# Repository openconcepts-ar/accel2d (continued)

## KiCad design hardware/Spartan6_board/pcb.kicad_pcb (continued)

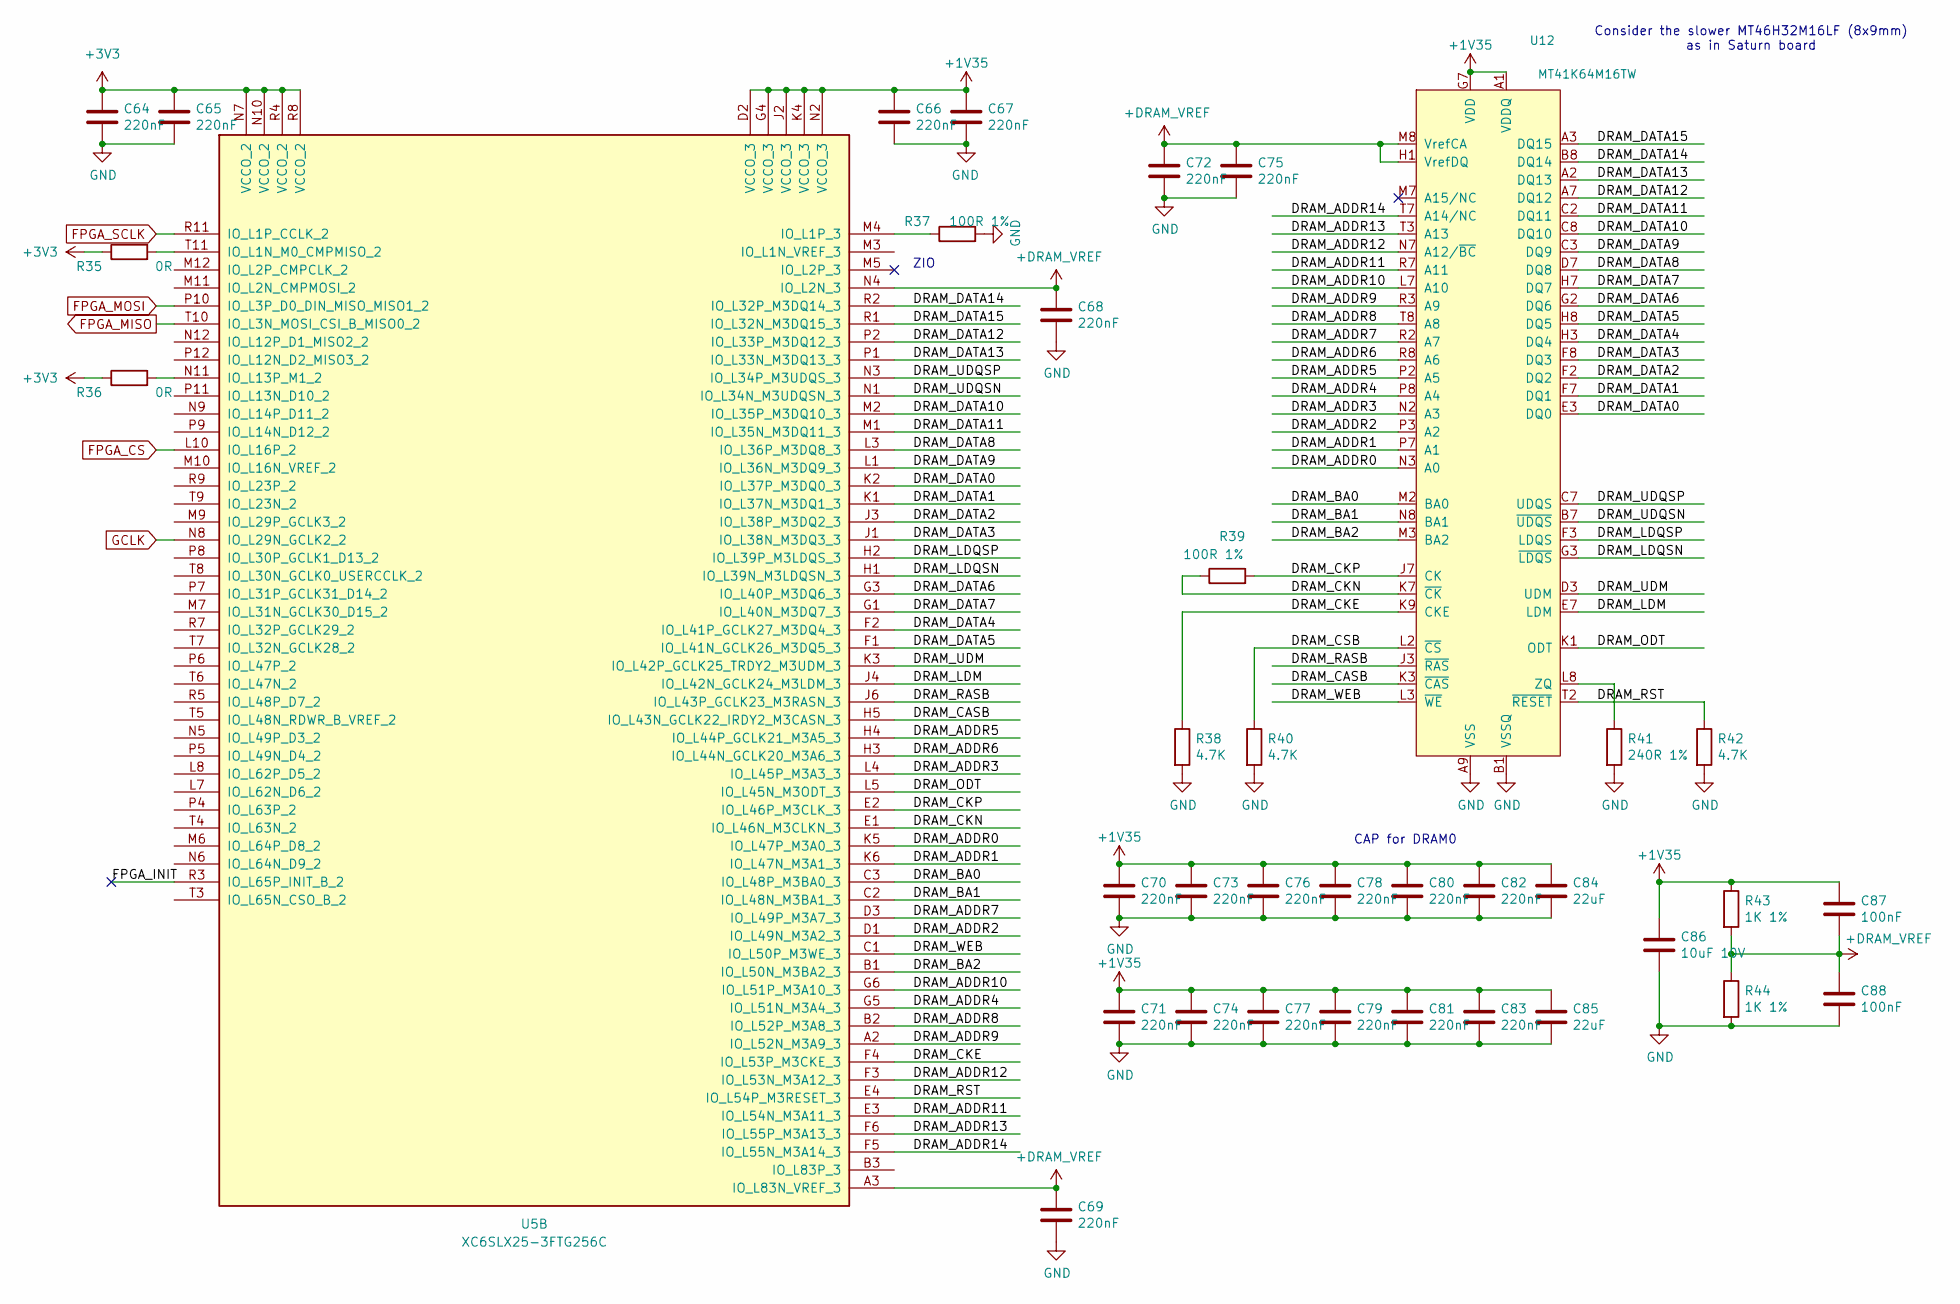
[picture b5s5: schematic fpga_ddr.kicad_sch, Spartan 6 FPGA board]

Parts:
C64, C65, C66, C67, C68, C69, C70, C71, C72, C73, C74, C75, C76, C77, C78, C79, C80, C81, C82, C83: 220nF; C_0402_1005Metric; LCSC C880414
C84, C85: 22uF; C_0603_1608Metric; LCSC Part Number C86295
C86: 10uF 10V; C_0805_2012Metric; LCSC Part Number C15850
C87, C88: 100nF; C_0402_1005Metric; LCSC C56392
R35, R36: 0R; R_0402_1005Metric; LCSC C105870
R37, R39: 100R 1%; R_0402_1005Metric
R38, R40, R42: 4.7K; R_0402_1005Metric; LCSC C105870
R41: 240R 1%; R_0402_1005Metric
R43, R44: 1K 1%; R_0402_1005Metric
U5: XC6SLX25-3FTG256C; Xilinx_FTG256; LCSC Part Number C1521716
U12: MT41K64M16TW; BGA-96_9.0x14.0mm_P0.8mm; LCSC Part Number C524855

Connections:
+1V35: C66.1, C67.1, C70.1, C71.1, C73.1, C74.1, C76.1, C77.1, C78.1, C79.1, C80.1, C81.1, C82.1, C83.1, C84.1, C85.1, C86.1, C87.1, R43.1, U5.D2 (VCCO_3), U5.G4 (VCCO_3), U5.J2 (VCCO_3), U5.K4 (VCCO_3), U5.N2 (VCCO_3), U12.A1 (VDDQ), U12.A8 (VDDQ), U12.B2 (VDD), U12.C1 (VDDQ), U12.C9 (VDDQ), U12.D2 (VDDQ), U12.D9 (VDD), U12.E9 (VDDQ), U12.F1 (VDDQ), U12.G7 (VDD), U12.H2 (VDDQ), U12.H9 (VDDQ), U12.K2 (VDD), U12.K8 (VDD), U12.N1 (VDD), U12.N9 (VDD), U12.R1 (VDD), U12.R9 (VDD); also elsewhere on the board
+3V3: C64.1, C65.1, R35.1, R36.1, U5.N7 (VCCO_2), U5.N10 (VCCO_2), U5.R4 (VCCO_2), U5.R8 (VCCO_2); also elsewhere on the board
+DRAM_VREF: C68.1, C69.1, C72.1, C75.1, C87.2, C88.1, R43.2, R44.1, U5.A3 (IO_L83N_VREF_3), U5.N4 (IO_L2N_3), U12.H1 (VrefDQ), U12.M8 (VrefCA)
/fpga_ddr/DRAM_ADDR0: U5.K5 (IO_L47P_M3A0_3), U12.N3 (A0)
/fpga_ddr/DRAM_ADDR1: U5.K6 (IO_L47N_M3A1_3), U12.P7 (A1)
/fpga_ddr/DRAM_ADDR2: U5.D1 (IO_L49N_M3A2_3), U12.P3 (A2)
/fpga_ddr/DRAM_ADDR3: U5.L4 (IO_L45P_M3A3_3), U12.N2 (A3)
/fpga_ddr/DRAM_ADDR4: U5.G5 (IO_L51N_M3A4_3), U12.P8 (A4)
/fpga_ddr/DRAM_ADDR5: U5.H4 (IO_L44P_GCLK21_M3A5_3), U12.P2 (A5)
/fpga_ddr/DRAM_ADDR6: U5.H3 (IO_L44N_GCLK20_M3A6_3), U12.R8 (A6)
/fpga_ddr/DRAM_ADDR7: U5.D3 (IO_L49P_M3A7_3), U12.R2 (A7)
/fpga_ddr/DRAM_ADDR8: U5.B2 (IO_L52P_M3A8_3), U12.T8 (A8)
/fpga_ddr/DRAM_ADDR9: U5.A2 (IO_L52N_M3A9_3), U12.R3 (A9)
/fpga_ddr/DRAM_ADDR10: U5.G6 (IO_L51P_M3A10_3), U12.L7 (A10)
/fpga_ddr/DRAM_ADDR11: U5.E3 (IO_L54N_M3A11_3), U12.R7 (A11)
/fpga_ddr/DRAM_ADDR12: U5.F3 (IO_L53N_M3A12_3), U12.N7 (A12/~BC)
/fpga_ddr/DRAM_ADDR13: U5.F6 (IO_L55P_M3A13_3), U12.T3 (A13)
/fpga_ddr/DRAM_ADDR14: U5.F5 (IO_L55N_M3A14_3), U12.T7 (A14/NC)
/fpga_ddr/DRAM_BA0: U5.C3 (IO_L48P_M3BA0_3), U12.M2 (BA0)
/fpga_ddr/DRAM_BA1: U5.C2 (IO_L48N_M3BA1_3), U12.N8 (BA1)
/fpga_ddr/DRAM_BA2: U5.B1 (IO_L50N_M3BA2_3), U12.M3 (BA2)
/fpga_ddr/DRAM_CASB: U5.H5 (IO_L43N_GCLK22_IRDY2_M3CASN_3), U12.K3 (~CAS)
/fpga_ddr/DRAM_CKE: R38.1, U5.F4 (IO_L53P_M3CKE_3), U12.K9 (CKE)
/fpga_ddr/DRAM_CKN: R39.1, U5.E1 (IO_L46N_M3CLKN_3), U12.K7 (~CK)
/fpga_ddr/DRAM_CKP: R39.2, U5.E2 (IO_L46P_M3CLK_3), U12.J7 (CK)
/fpga_ddr/DRAM_CSB: R40.1, U12.L2 (~CS)
/fpga_ddr/DRAM_DATA0: U5.K2 (IO_L37P_M3DQ0_3), U12.E3 (DQ0)
/fpga_ddr/DRAM_DATA1: U5.K1 (IO_L37N_M3DQ1_3), U12.F7 (DQ1)
/fpga_ddr/DRAM_DATA2: U5.J3 (IO_L38P_M3DQ2_3), U12.F2 (DQ2)
/fpga_ddr/DRAM_DATA3: U5.J1 (IO_L38N_M3DQ3_3), U12.F8 (DQ3)
/fpga_ddr/DRAM_DATA4: U5.F2 (IO_L41P_GCLK27_M3DQ4_3), U12.H3 (DQ4)
/fpga_ddr/DRAM_DATA5: U5.F1 (IO_L41N_GCLK26_M3DQ5_3), U12.H8 (DQ5)
/fpga_ddr/DRAM_DATA6: U5.G3 (IO_L40P_M3DQ6_3), U12.G2 (DQ6)
/fpga_ddr/DRAM_DATA7: U5.G1 (IO_L40N_M3DQ7_3), U12.H7 (DQ7)
/fpga_ddr/DRAM_DATA8: U5.L3 (IO_L36P_M3DQ8_3), U12.D7 (DQ8)
/fpga_ddr/DRAM_DATA9: U5.L1 (IO_L36N_M3DQ9_3), U12.C3 (DQ9)
/fpga_ddr/DRAM_DATA10: U5.M2 (IO_L35P_M3DQ10_3), U12.C8 (DQ10)
/fpga_ddr/DRAM_DATA11: U5.M1 (IO_L35N_M3DQ11_3), U12.C2 (DQ11)
/fpga_ddr/DRAM_DATA12: U5.P2 (IO_L33P_M3DQ12_3), U12.A7 (DQ12)
/fpga_ddr/DRAM_DATA13: U5.P1 (IO_L33N_M3DQ13_3), U12.A2 (DQ13)
/fpga_ddr/DRAM_DATA14: U5.R2 (IO_L32P_M3DQ14_3), U12.B8 (DQ14)
/fpga_ddr/DRAM_DATA15: U5.R1 (IO_L32N_M3DQ15_3), U12.A3 (DQ15)
/fpga_ddr/DRAM_LDM: U5.J4 (IO_L42N_GCLK24_M3LDM_3), U12.E7 (LDM)
/fpga_ddr/DRAM_LDQSN: U5.H1 (IO_L39N_M3LDQSN_3), U12.G3 (~LDQS)
/fpga_ddr/DRAM_LDQSP: U5.H2 (IO_L39P_M3LDQS_3), U12.F3 (LDQS)
/fpga_ddr/DRAM_ODT: U5.L5 (IO_L45N_M3ODT_3), U12.K1 (ODT)
/fpga_ddr/DRAM_RASB: U5.J6 (IO_L43P_GCLK23_M3RASN_3), U12.J3 (~RAS)
/fpga_ddr/DRAM_RST: R42.1, U5.E4 (IO_L54P_M3RESET_3), U12.T2 (~RESET)
/fpga_ddr/DRAM_UDM: U5.K3 (IO_L42P_GCLK25_TRDY2_M3UDM_3), U12.D3 (UDM)
/fpga_ddr/DRAM_UDQSN: U5.N1 (IO_L34N_M3UDQSN_3), U12.B7 (~UDQS)
/fpga_ddr/DRAM_UDQSP: U5.N3 (IO_L34P_M3UDQS_3), U12.C7 (UDQS)
/fpga_ddr/DRAM_WEB: U5.C1 (IO_L50P_M3WE_3), U12.L3 (~WE)
/fpga_ddr/FPGA_INIT: U5.R3 (IO_L65P_INIT_B_2)
FPGA_CS: U5.L10 (IO_L16P_2); also elsewhere on the board
FPGA_MISO: U5.T10 (IO_L3N_MOSI_CSI_B_MISO0_2); also elsewhere on the board
FPGA_MOSI: U5.P10 (IO_L3P_D0_DIN_MISO_MISO1_2); also elsewhere on the board
FPGA_SCLK: U5.R11 (IO_L1P_CCLK_2); also elsewhere on the board
GCLK: U5.N8 (IO_L29N_GCLK2_2); also elsewhere on the board
GND: C64.2, C65.2, C66.2, C67.2, C68.2, C69.2, C70.2, C71.2, C72.2, C73.2, C74.2, C75.2, C76.2, C77.2, C78.2, C79.2, C80.2, C81.2, C82.2, C83.2, C84.2, C85.2, C86.2, C88.2, R37.2, R38.2, R40.2, R41.2, R42.2, R44.2, U12.A9 (VSS), U12.B1 (VSSQ), U12.B3 (VSS), U12.B9 (VSSQ), U12.D1 (VSSQ), U12.D8 (VSSQ), U12.E1 (VSS), U12.E2 (VSSQ), U12.E8 (VSSQ), U12.F9 (VSSQ), U12.G1 (VSSQ), U12.G8 (VSS), U12.G9 (VSSQ), U12.J1 (VSS), U12.J2 (VSS), U12.J8 (VSS), U12.J9 (VSS), U12.L1 (VSS), U12.L9 (VSS), U12.M1 (VSS), U12.M9 (VSS), U12.P1 (VSS), U12.P9 (VSS), U12.T1 (VSS), U12.T9 (VSS); also elsewhere on the board
unnamed: R35.2, U5.T11 (IO_L1N_M0_CMPMISO_2)
unnamed: R37.1, U5.M4 (IO_L1P_3)
unnamed: R36.2, U5.N11 (IO_L13P_M1_2)
unnamed: R41.1, U12.L8 (ZQ)

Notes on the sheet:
Consider the slower MT46H32M16LF (8x9mm) as in Saturn board
ZIO
CAP for DRAM0

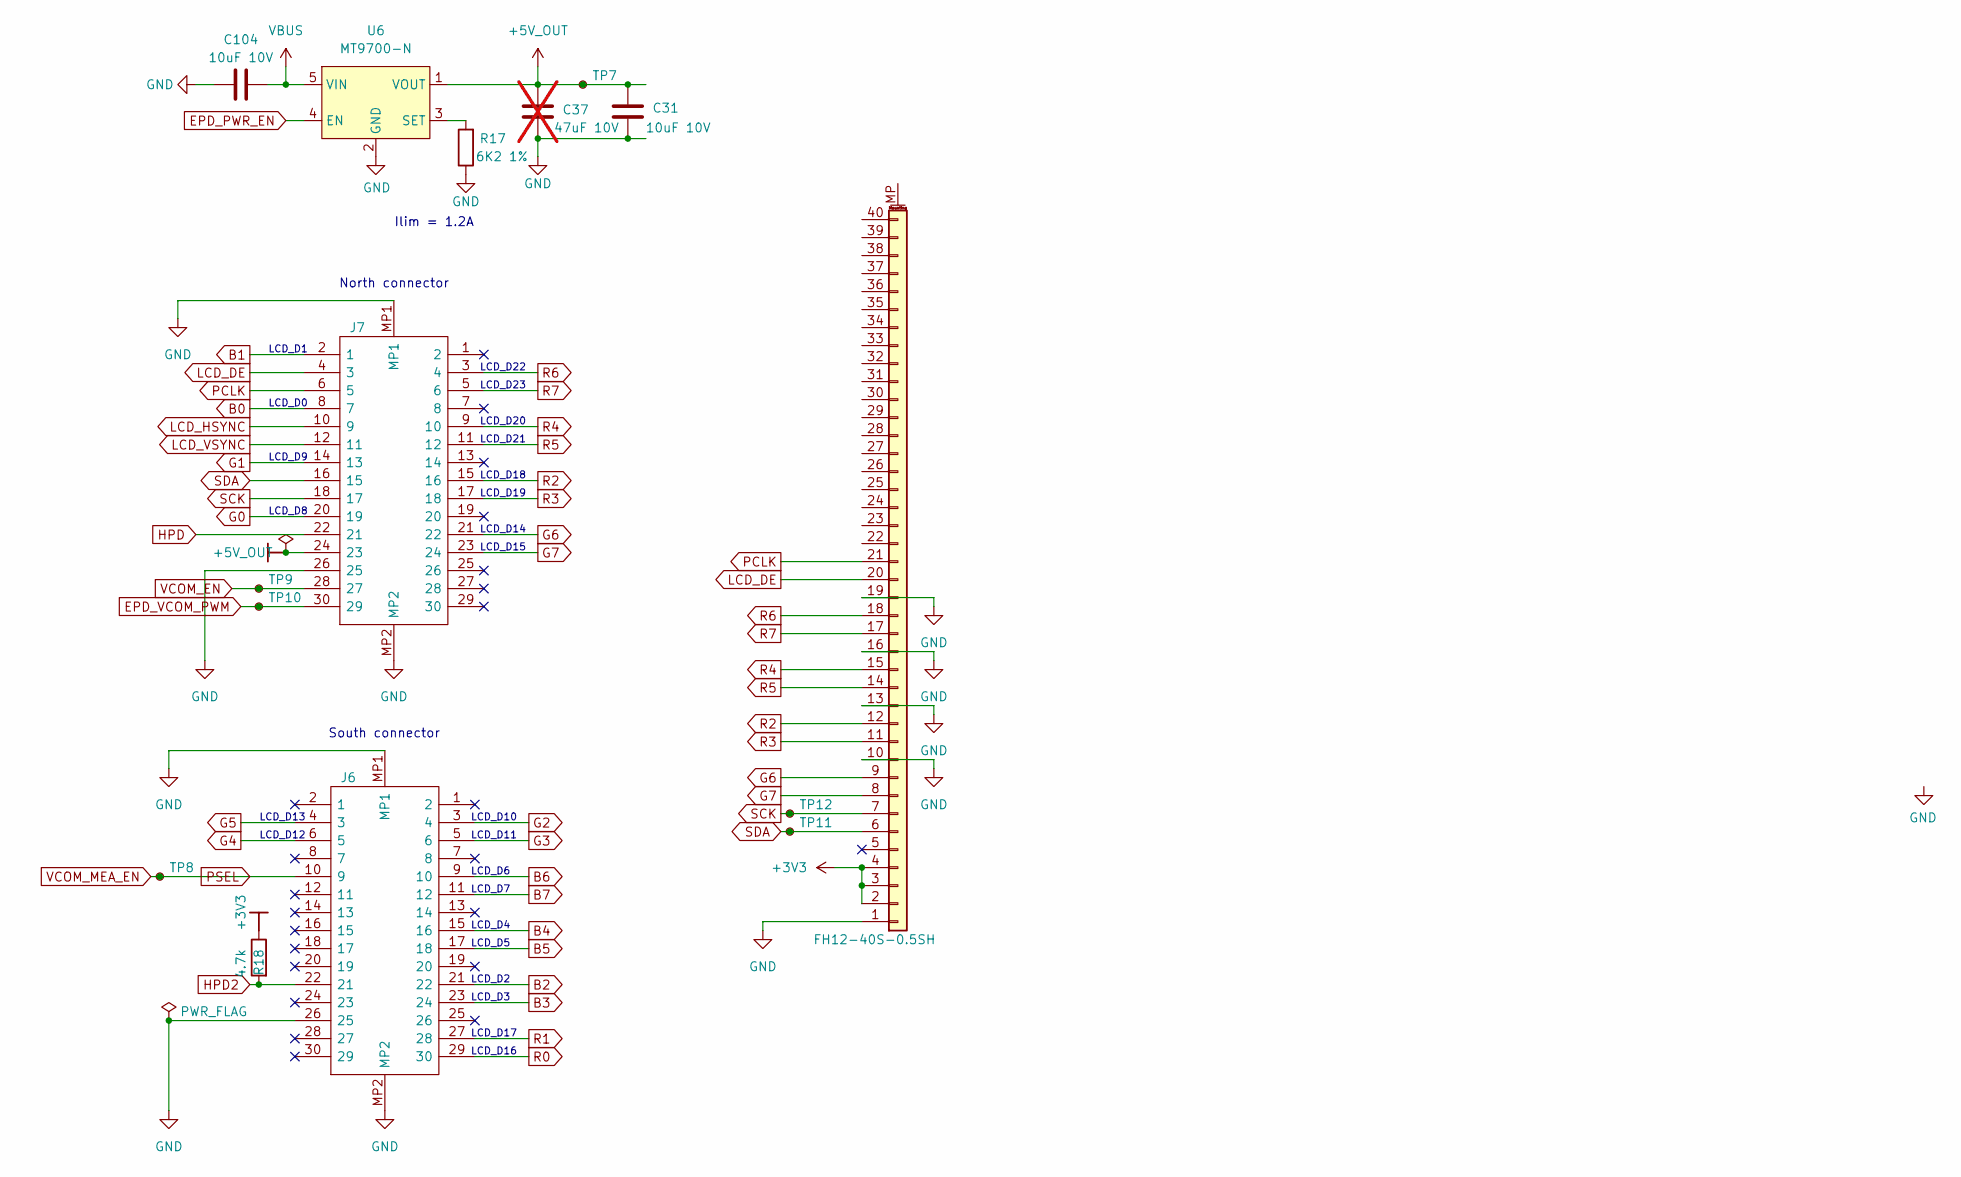
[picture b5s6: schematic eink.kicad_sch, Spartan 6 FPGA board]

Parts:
C31, C104: 10uF 10V; C_0805_2012Metric
C37: 47uF 10V; C_1206_3216Metric; LCSC Part Number C96123; not fitted
J3: FH12-40S-0.5SH; Hirose_FH12-40S-0.5SH_1x40-1MP_P0.50mm_Horizontal_Reversed; MPN FH12-40S-0.5SH
J6, J7: DF12NB(3.0)-30DS-0.5V(51); DF12NB3030DP05V51; MPN DF12NB(3.0)-30DS-0.5V(51)
R17: 6K2 1%; R_0402_1005Metric
R18: 4.7k; R_0402_1005Metric; LCSC Part Number C25940
TP7, TP8, TP9, TP10, TP11, TP12: TestPoint_Small; TestPoint_Pad_D1.5mm
U6: MT9700-N; SOT-23-5; MPN MT9700-N; LCSC Part Number C42441843

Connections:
+3V3: J3.2, J3.3, J3.4, R18.1; also elsewhere on the board
+5V_OUT: C31.1, C37.2, J7.24 (23), TP7.1, U6.1 (VOUT)
B0: J7.8 (7); also elsewhere on the board
B1: J7.2 (1); also elsewhere on the board
B2: J6.21 (22); also elsewhere on the board
B3: J6.23 (24); also elsewhere on the board
B4: J6.15 (16); also elsewhere on the board
B5: J6.17 (18); also elsewhere on the board
B6: J6.9 (10); also elsewhere on the board
B7: J6.11 (12); also elsewhere on the board
EPD_PWR_EN: U6.4 (EN); also elsewhere on the board
EPD_VCOM_PWM: J7.30 (29), TP10.1; also elsewhere on the board
G0: J7.20 (19); also elsewhere on the board
G1: J7.14 (13); also elsewhere on the board
G2: J6.3 (4); also elsewhere on the board
G3: J6.5 (6); also elsewhere on the board
G4: J6.6 (5); also elsewhere on the board
G5: J6.4 (3); also elsewhere on the board
G6: J3.9, J7.21 (22); also elsewhere on the board
G7: J3.8, J7.23 (24); also elsewhere on the board
GND: C31.2, C37.1, C104.1, J3.1, J3.10, J3.13, J3.16, J3.19, J6.26 (25), J6.MP1, J6.MP2, J7.26 (25), J7.MP1, J7.MP2, R17.1, U6.2 (GND); also elsewhere on the board
HPD: J7.22 (21)
HPD2: J6.22 (21), R18.2
LCD_DE: J3.20, J7.4 (3); also elsewhere on the board
LCD_HSYNC: J7.10 (9); also elsewhere on the board
LCD_VSYNC: J7.12 (11); also elsewhere on the board
unnamed: R17.2, U6.3 (SET)
PCLK: J3.21, J7.6 (5); also elsewhere on the board
PSEL: J6.10 (9), TP8.1; also elsewhere on the board
R2: J3.12, J7.15 (16); also elsewhere on the board
R3: J3.11, J7.17 (18); also elsewhere on the board
R4: J3.15, J7.9 (10); also elsewhere on the board
R5: J3.14, J7.11 (12); also elsewhere on the board
R6: J3.18, J7.3 (4); also elsewhere on the board
R7: J3.17, J7.5 (6); also elsewhere on the board
SCK: J3.7, J7.18 (17), TP12.1
SDA: J3.6, J7.16 (15), TP11.1
VBUS: C104.2, U6.5 (VIN); also elsewhere on the board
VCOM_EN: J7.28 (27), TP9.1; also elsewhere on the board

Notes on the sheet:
LCD_D0
Ilim = 1.2A
LCD_D17
South connector
LCD_D11
LCD_D4
LCD_D3
LCD_D8
LCD_D10
LCD_D19
LCD_D23
LCD_D20
North connector
LCD_D5
LCD_D13
LCD_D18
LCD_D21
LCD_D22
LCD_D7
LCD_D6
LCD_D15
LCD_D1
LCD_D12
LCD_D9
LCD_D16
LCD_D2
LCD_D14

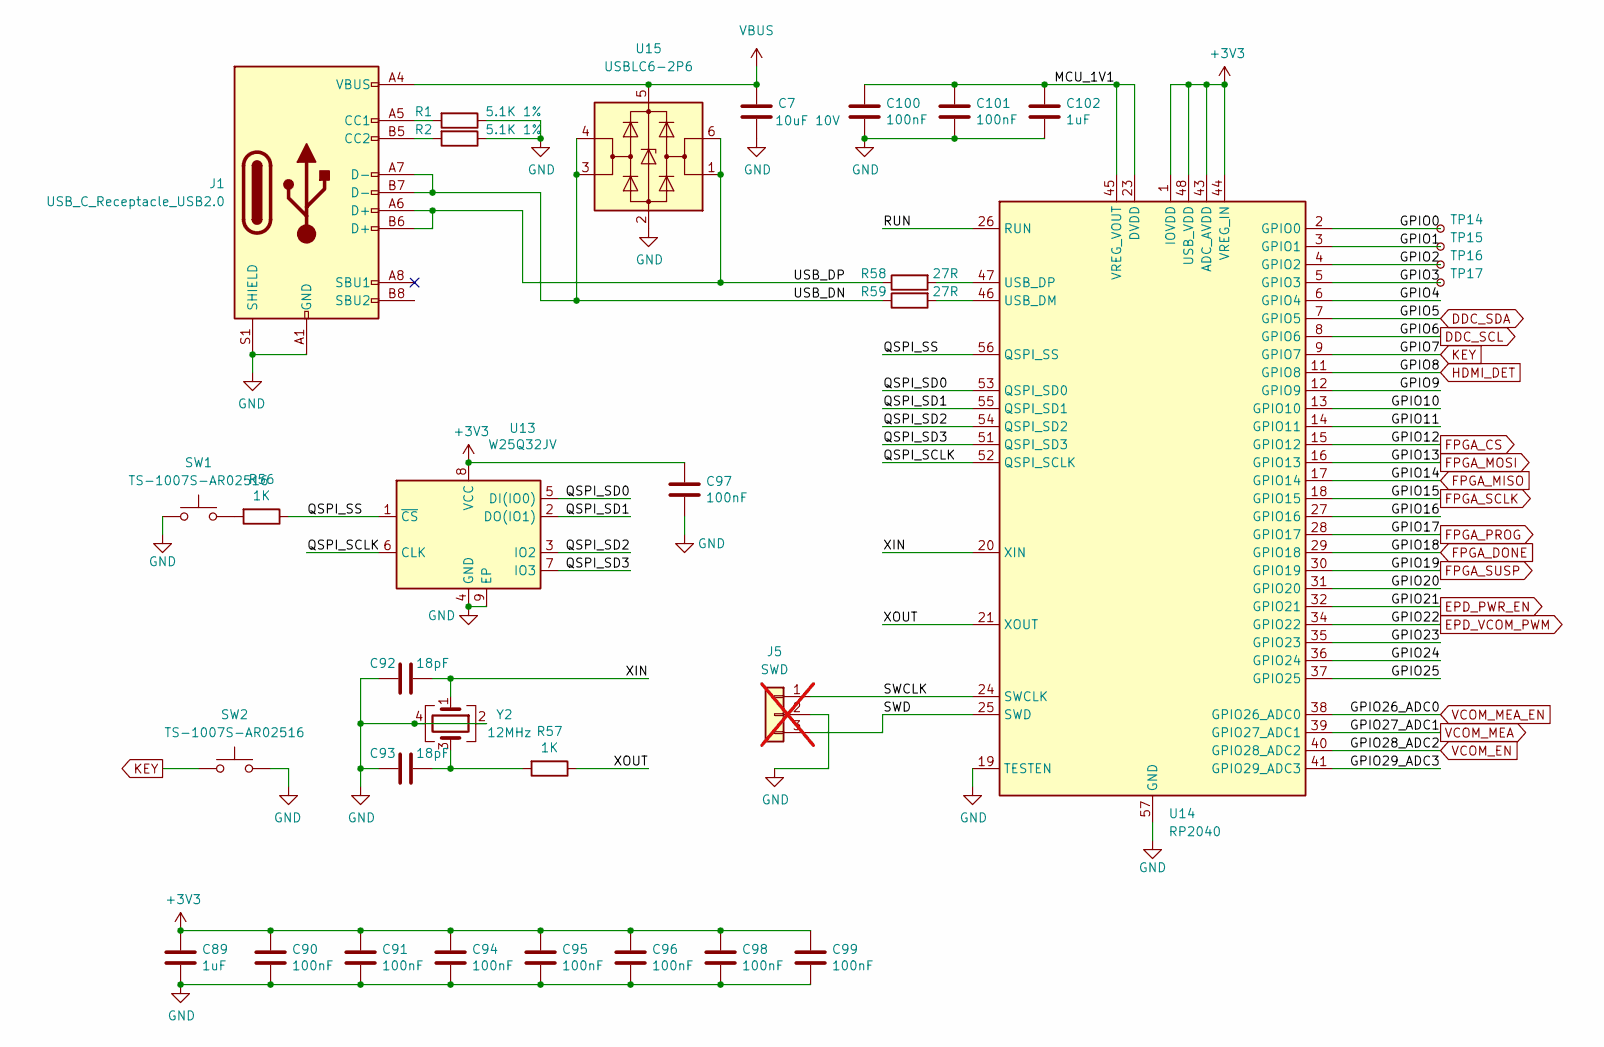
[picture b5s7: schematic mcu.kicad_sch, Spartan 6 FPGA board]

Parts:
C7: 10uF 10V; C_0805_2012Metric; LCSC Part Number C32635
C89, C102: 1uF; C_0402_1005Metric
C90, C91, C94, C95, C96, C97, C98, C99, C100, C101: 100nF; C_0402_1005Metric
C92, C93: 18pF; C_0402_1005Metric
J1: USB_C_Receptacle_USB2.0; USB_C_Receptacle_HRO_TYPE-C-31-M-12; MPN TYPE-C-31-M-12
J5: SWD; PinHeader_1x03_P2.54mm_Vertical; not fitted
R1, R2: 5.1K 1%; R_0402_1005Metric
R56, R57: 1K; R_0402_1005Metric
R58, R59: 27R; R_0402_1005Metric
SW1, SW2: TS-1007S-AR02516; SW_SPST_CK_RS282G05A3; MPN TS-1007S-AR02516
TP14, TP15, TP16, TP17: TestPoint_Small; TestPoint_Pad_D1.5mm
U13: W25Q32JV; WSON-8-1EP_6x5mm_P1.27mm_EP3.4x4.3mm; LCSC Part Number C571260
U14: RP2040; RP2040-QFN-56; LCSC Part Number C2040
U15: USBLC6-2P6; SOT-666-6_L1.6-W1.2-P0.50-LS1.6-BR; MPN USBLC6-2P6
Y2: 12MHz; Oscillator_SMD_Abracon_ASE-4Pin_3.2x2.5mm; MPN X322512MSB4SI

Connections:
+3V3: C89.1, C90.1, C91.1, C94.1, C95.1, C96.1, C97.1, C98.1, C99.1, U13.8 (VCC), U14.1 (IOVDD), U14.10 (IOVDD), U14.22 (IOVDD), U14.33 (IOVDD), U14.42 (IOVDD), U14.43 (ADC_AVDD), U14.44 (VREG_IN), U14.48 (USB_VDD), U14.49 (IOVDD); also elsewhere on the board
/mcu/GPIO0: TP14.1, U14.2 (GPIO0)
/mcu/GPIO1: TP15.1, U14.3 (GPIO1)
/mcu/GPIO2: TP16.1, U14.4 (GPIO2)
/mcu/GPIO3: TP17.1, U14.5 (GPIO3)
/mcu/GPIO4: U14.6 (GPIO4)
/mcu/GPIO9: U14.12 (GPIO9)
/mcu/GPIO10: U14.13 (GPIO10)
/mcu/GPIO11: U14.14 (GPIO11)
/mcu/GPIO16: U14.27 (GPIO16)
/mcu/GPIO20: U14.31 (GPIO20)
/mcu/GPIO23: U14.35 (GPIO23)
/mcu/GPIO24: U14.36 (GPIO24)
/mcu/GPIO25: U14.37 (GPIO25)
/mcu/GPIO29_ADC3: U14.41 (GPIO29_ADC3)
/mcu/MCU_1V1: C100.1, C101.1, C102.1, U14.23 (DVDD), U14.45 (VREG_VOUT), U14.50 (DVDD)
/mcu/QSPI_SCLK: U13.6 (CLK), U14.52 (QSPI_SCLK)
/mcu/QSPI_SD0: U13.5 (DI(IO0)), U14.53 (QSPI_SD0)
/mcu/QSPI_SD1: U13.2 (DO(IO1)), U14.55 (QSPI_SD1)
/mcu/QSPI_SD2: U13.3 (IO2), U14.54 (QSPI_SD2)
/mcu/QSPI_SD3: U13.7 (IO3), U14.51 (QSPI_SD3)
/mcu/QSPI_SS: R56.1, U13.1 (~CS), U14.56 (QSPI_SS)
/mcu/RUN: U14.26 (RUN)
/mcu/SWCLK: J5.1, U14.24 (SWCLK)
/mcu/SWD: J5.3, U14.25 (SWD)
/mcu/USB_DN: J1.A7 (D-), J1.B7 (D-), R59.1, U15.3 (I/O2), U15.4 (I/O2)
/mcu/USB_DP: J1.A6 (D+), J1.B6 (D+), R58.1, U15.1 (I/O1), U15.6 (I/O1)
/mcu/XIN: C92.1, U14.20 (XIN), Y2.1
/mcu/XOUT: R57.1, U14.21 (XOUT)
DDC_SCL: U14.8 (GPIO6); also elsewhere on the board
DDC_SDA: U14.7 (GPIO5); also elsewhere on the board
EPD_PWR_EN: U14.32 (GPIO21); also elsewhere on the board
EPD_VCOM_PWM: U14.34 (GPIO22); also elsewhere on the board
FPGA_CS: U14.15 (GPIO12); also elsewhere on the board
FPGA_DONE: U14.29 (GPIO18); also elsewhere on the board
FPGA_MISO: U14.17 (GPIO14); also elsewhere on the board
FPGA_MOSI: U14.16 (GPIO13); also elsewhere on the board
FPGA_PROG: U14.28 (GPIO17); also elsewhere on the board
FPGA_SCLK: U14.18 (GPIO15); also elsewhere on the board
FPGA_SUSP: U14.30 (GPIO19); also elsewhere on the board
GND: C7.2, C89.2, C90.2, C91.2, C92.2, C93.2, C94.2, C95.2, C96.2, C97.2, C98.2, C99.2, C100.2, C101.2, C102.2, J1.A1 (GND), J1.A12 (GND), J1.B1 (GND), J1.B12 (GND), J1.S1 (SHIELD), J5.2, R1.1, R2.1, SW1.2, SW2.1, U13.4 (GND), U13.9 (EP), U14.19 (TESTEN), U14.57 (GND), U15.2 (GND), Y2.2, Y2.4; also elsewhere on the board
HDMI_DET: U14.11 (GPIO8); also elsewhere on the board
KEY: SW2.2, U14.9 (GPIO7)
unnamed: C93.1, R57.2, Y2.3
unnamed: J1.A5 (CC1), R1.2
unnamed: J1.B5 (CC2), R2.2
unnamed: R56.2, SW1.1
unnamed: R59.2, U14.46 (USB_DM)
unnamed: R58.2, U14.47 (USB_DP)
PSEL: U14.38 (GPIO26_ADC0); also elsewhere on the board
VBUS: C7.1, J1.A4 (VBUS), J1.A9 (VBUS), J1.B4 (VBUS), J1.B9 (VBUS), U15.5 (VBUS); also elsewhere on the board
VCOM_EN: U14.40 (GPIO28_ADC2); also elsewhere on the board
VCOM_MEA: U14.39 (GPIO27_ADC1)

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
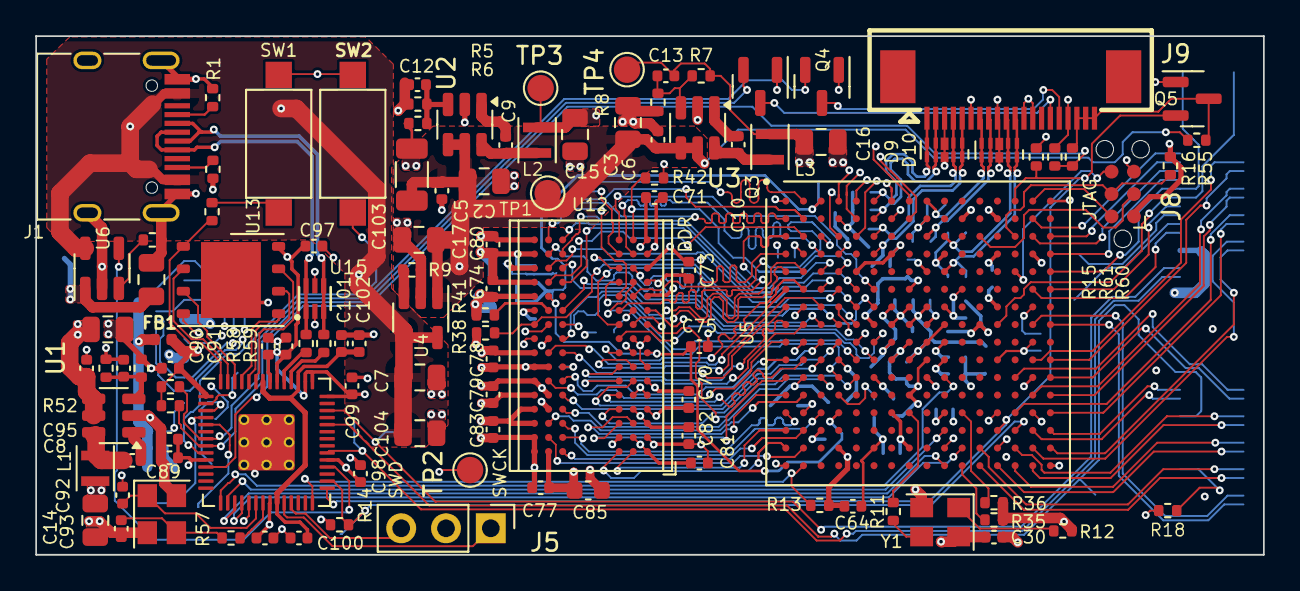
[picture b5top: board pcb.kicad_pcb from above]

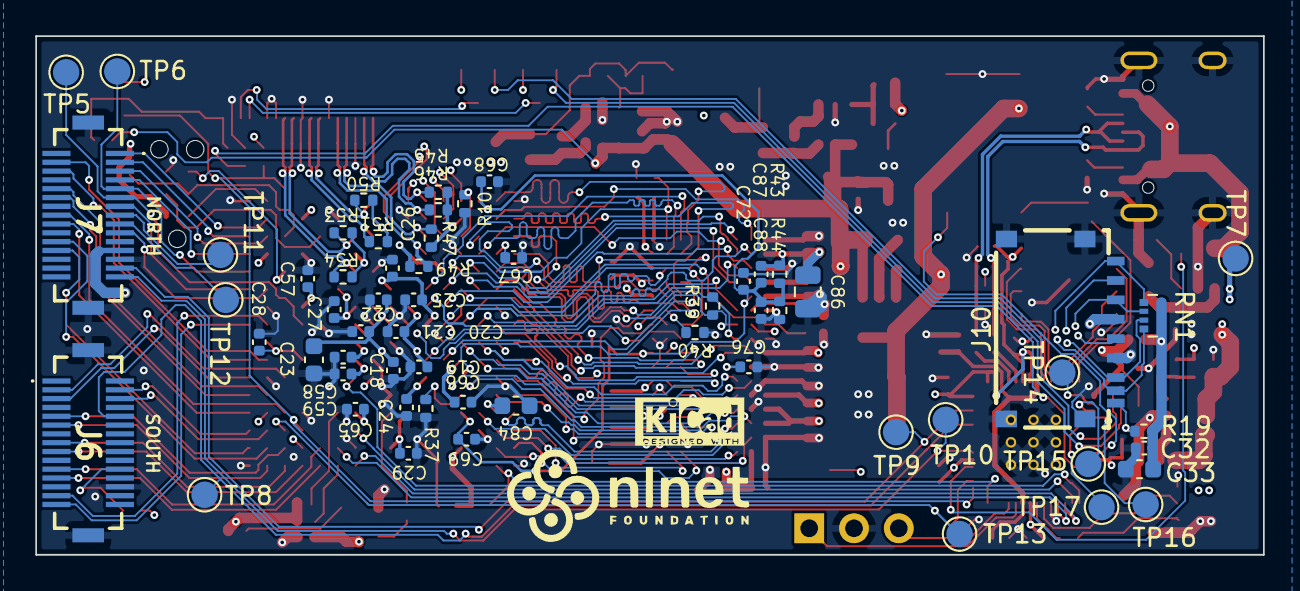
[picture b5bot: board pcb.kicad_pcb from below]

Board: 4 copper layers, 69.6 x 29.4 mm, 171 parts (60 on the bottom side), 168 nets.
